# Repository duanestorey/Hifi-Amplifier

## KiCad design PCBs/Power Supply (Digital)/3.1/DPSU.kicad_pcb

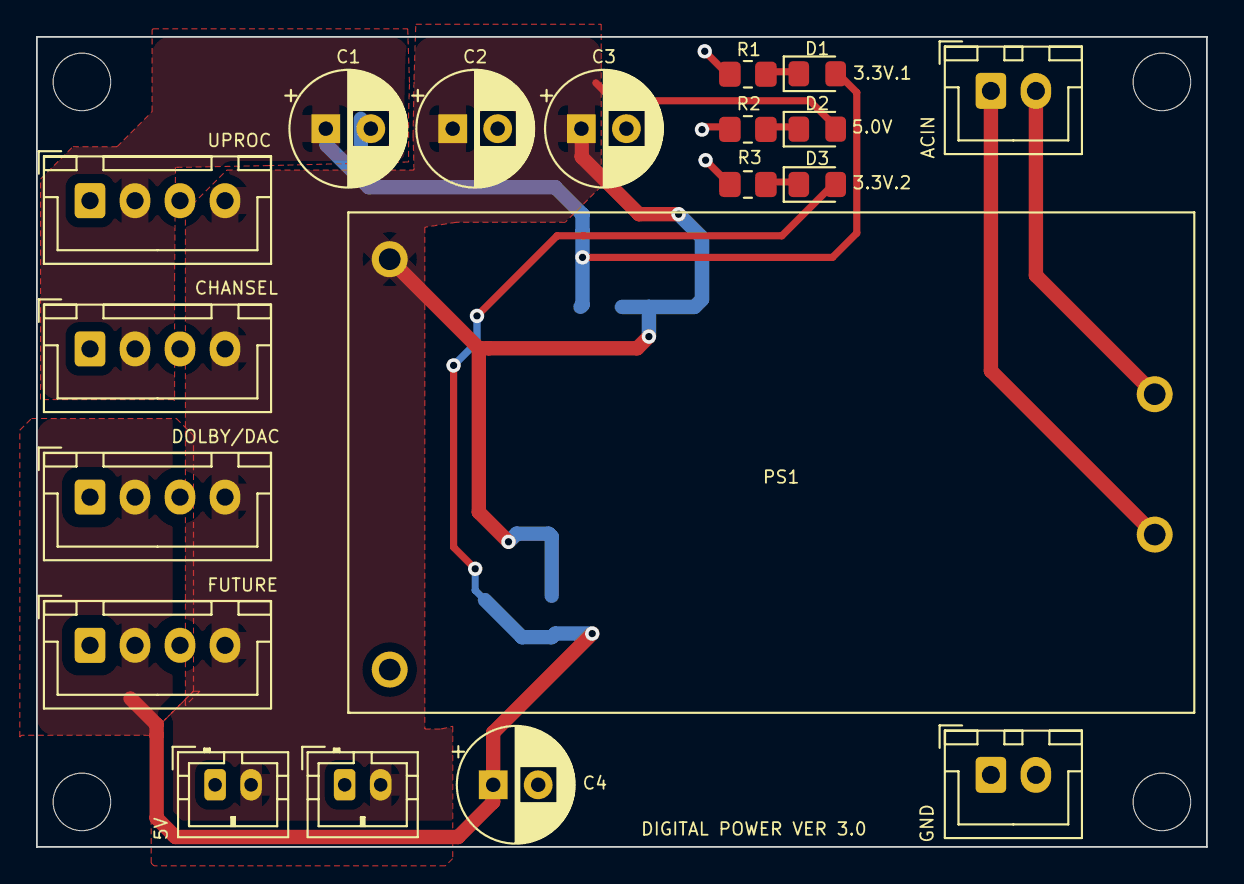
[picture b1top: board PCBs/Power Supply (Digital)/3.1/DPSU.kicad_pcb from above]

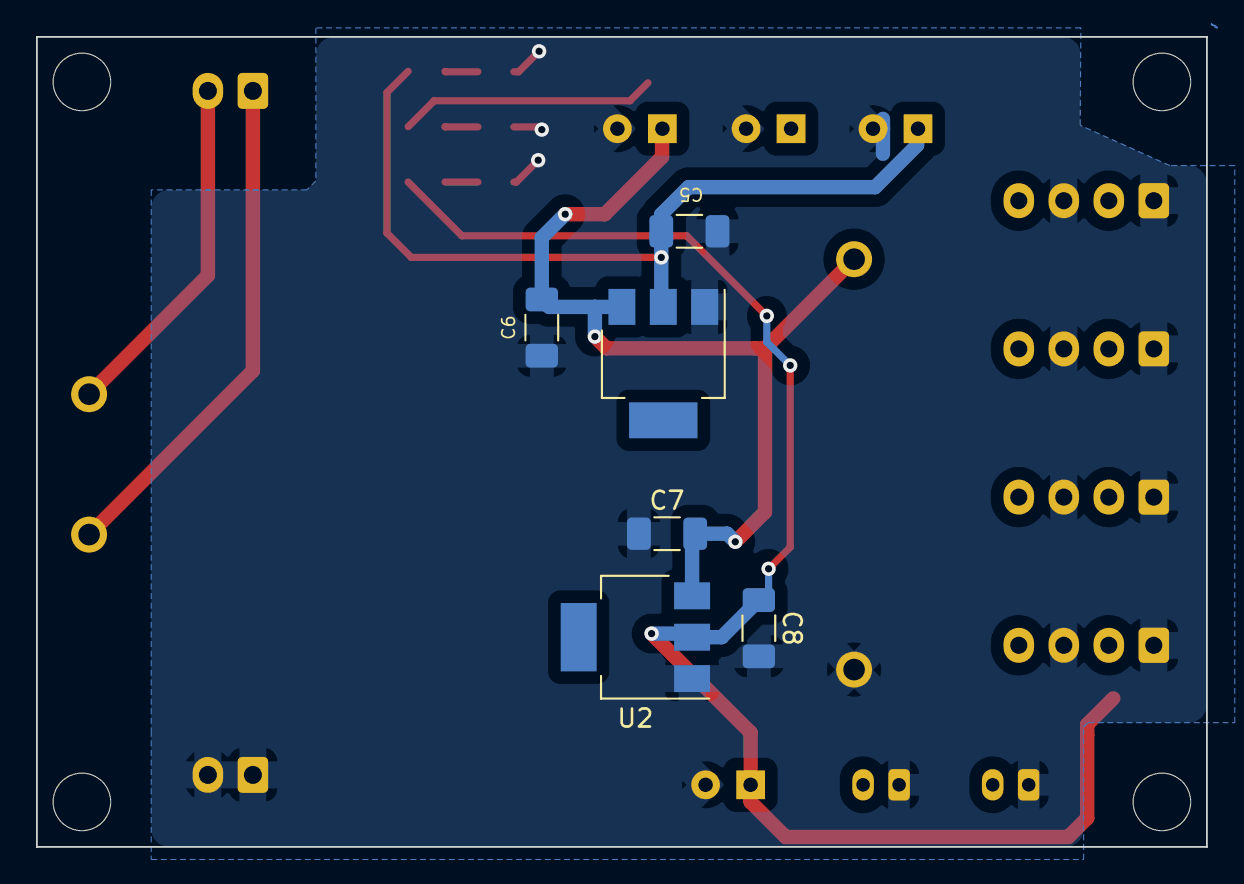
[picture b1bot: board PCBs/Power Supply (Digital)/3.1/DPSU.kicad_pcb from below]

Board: 2 copper layers, 65.0 x 45.0 mm, 29 parts (6 on the bottom side), 9 nets.

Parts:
C1, C2, C3, C4: 470u 10V; CP_Radial_D6.3mm_P2.50mm
C5, C8: 10U; C_1206_3216Metric_Pad1.33x1.80mm_HandSolder
C6, C7: 10u; C_1206_3216Metric_Pad1.33x1.80mm_HandSolder
D1, D3: WHITE; LED_0805_2012Metric_Pad1.15x1.40mm_HandSolder
D2: BLUE; LED_0805_2012Metric_Pad1.15x1.40mm_HandSolder
DIG1, DIG2: Conn_01x02_Male; JST_PH_B2B-PH-K_1x02_P2.00mm_Vertical
H1, H2, H3, H4: MountingHole; MountingHole_3.2mm_M3
J1: FUTURE; JST_XH_B4B-XH-A_1x04_P2.50mm_Vertical
J2: CHANSEL; JST_XH_B4B-XH-A_1x04_P2.50mm_Vertical
J3: DOLBY; JST_XH_B4B-XH-A_1x04_P2.50mm_Vertical
J4: UPRO; JST_XH_B4B-XH-A_1x04_P2.50mm_Vertical
J5, J6: Conn_01x02_Male; JST_XH_B2B-XH-A_1x02_P2.50mm_Vertical
PS1: HLK-10M05
R1, R3: 510R; R_0805_2012Metric_Pad1.20x1.40mm_HandSolder
R2: 750R; R_0805_2012Metric_Pad1.20x1.40mm_HandSolder
U1, U2: AZ1117CH2-3.3; SOT-223

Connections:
3V3: C1.1, C5.1, D1.2 (A), J1.2, J2.2, U1.2 (VO)
3V32: C4.1, C8.1, D3.2 (A), J3.2, J4.2, U2.2 (VO)
5V: C2.1, C3.1, C6.2, C7.2, D2.2 (A), DIG1.2, DIG2.2, J1.4, J2.4, J3.4, J4.4, PS1.4 (+Vout), U1.3 (VI), U2.3 (VI)
unnamed: D1.1 (K), R1.1
unnamed: D2.1 (K), R2.1
unnamed: D3.1 (K), R3.1
PGND: C1.2, C2.2, C3.2, C4.2, C5.2, C6.1, C7.1, C8.2, DIG1.1, DIG2.1, J1.1, J1.3, J2.1, J2.3, J3.1, J3.3, J4.1, J4.3, J5.1, J5.2, PS1.3 (-Vout), R1.2, R2.2, R3.2, U1.1 (GND), U2.1 (GND)
VIN: J6.1, PS1.1 (AC/L)
VNEG: J6.2, PS1.2 (AC/N)

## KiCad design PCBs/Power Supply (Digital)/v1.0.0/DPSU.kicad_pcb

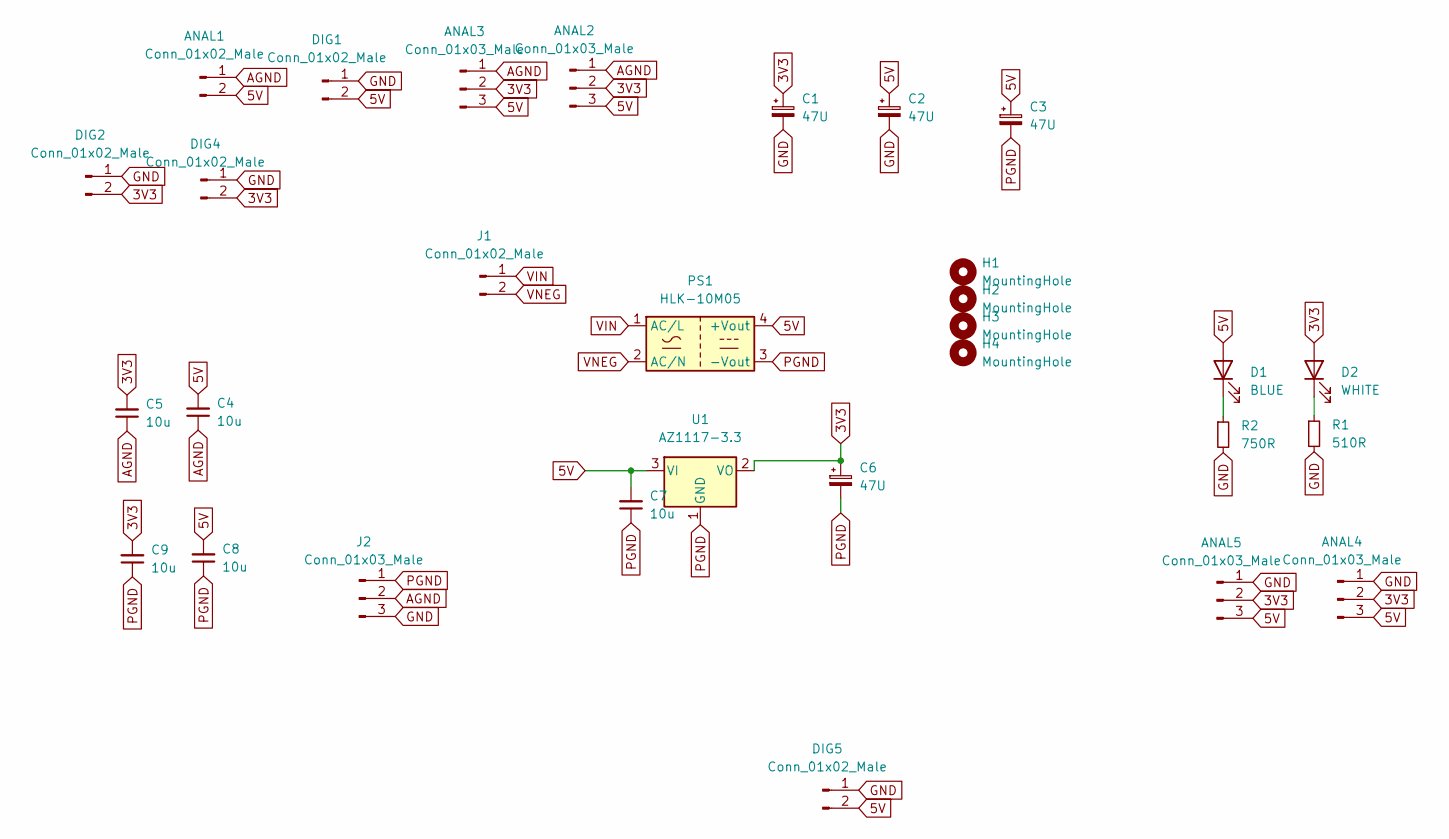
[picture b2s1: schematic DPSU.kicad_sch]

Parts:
ANAL1: Conn_01x02_Male; JST_PH_B2B-PH-K_1x02_P2.00mm_Vertical
ANAL2, ANAL3, ANAL4, ANAL5: Conn_01x03_Male; JST_PH_B3B-PH-K_1x03_P2.00mm_Vertical
C1, C2: 47U; CP_Radial_D6.3mm_P2.50mm
C3, C6: 47U; CP_Radial_D8.0mm_P5.00mm
C4, C5, C7, C8, C9: 10u; C_1206_3216Metric_Pad1.33x1.80mm_HandSolder
D1: BLUE; LED_0805_2012Metric_Pad1.15x1.40mm_HandSolder
D2: WHITE; LED_0805_2012Metric_Pad1.15x1.40mm_HandSolder
DIG1, DIG2, DIG4, DIG5: Conn_01x02_Male; JST_PH_B2B-PH-K_1x02_P2.00mm_Vertical
H1, H2, H3, H4: MountingHole; MountingHole_3.2mm_M3
J1: Conn_01x02_Male; JST_XH_B2B-XH-A_1x02_P2.50mm_Vertical
J2: Conn_01x03_Male; JST_PH_B3B-PH-K_1x03_P2.00mm_Vertical
PS1: HLK-10M05
R1: 510R; R_0805_2012Metric_Pad1.20x1.40mm_HandSolder
R2: 750R; R_0805_2012Metric_Pad1.20x1.40mm_HandSolder
U1: AZ1117-3.3; SOT-223

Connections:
3V3: ANAL2.2, ANAL3.2, ANAL4.2, ANAL5.2, C1.1, C5.2, C6.1, C9.2, D2.2 (A), DIG2.2, DIG4.2, U1.2 (VO)
5V: ANAL1.2, ANAL2.3, ANAL3.3, ANAL4.3, ANAL5.3, C2.1, C3.1, C4.2, C7.2, C8.2, D1.2 (A), DIG1.2, DIG5.2, PS1.4 (+Vout), U1.3 (VI)
AGND: ANAL1.1, ANAL2.1, ANAL3.1, C4.1, C5.1, J2.2
GND: ANAL4.1, ANAL5.1, C1.2, C2.2, DIG1.1, DIG2.1, DIG4.1, DIG5.1, J2.3, R1.2, R2.2
unnamed: D1.1 (K), R2.1
unnamed: D2.1 (K), R1.1
PGND: C3.2, C6.2, C7.1, C8.1, C9.1, J2.1, PS1.3 (-Vout), U1.1 (GND)
VIN: J1.1, PS1.1 (AC/L)
VNEG: J1.2, PS1.2 (AC/N)

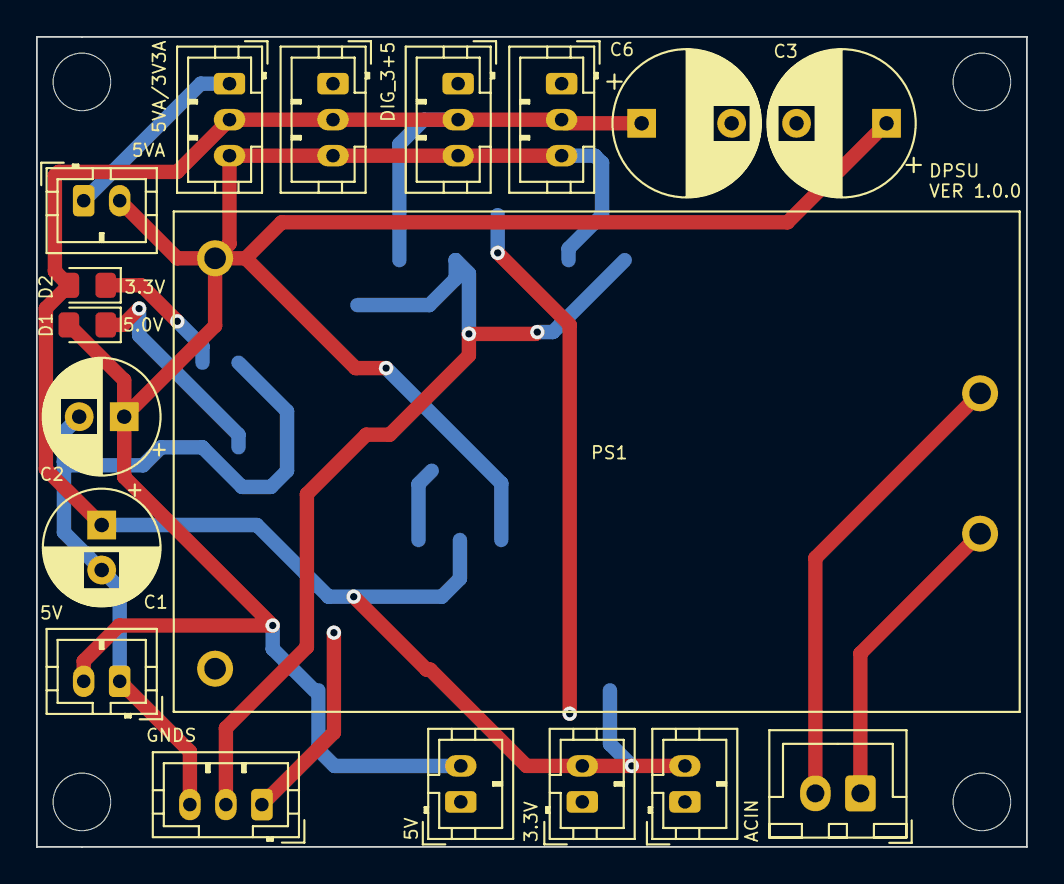
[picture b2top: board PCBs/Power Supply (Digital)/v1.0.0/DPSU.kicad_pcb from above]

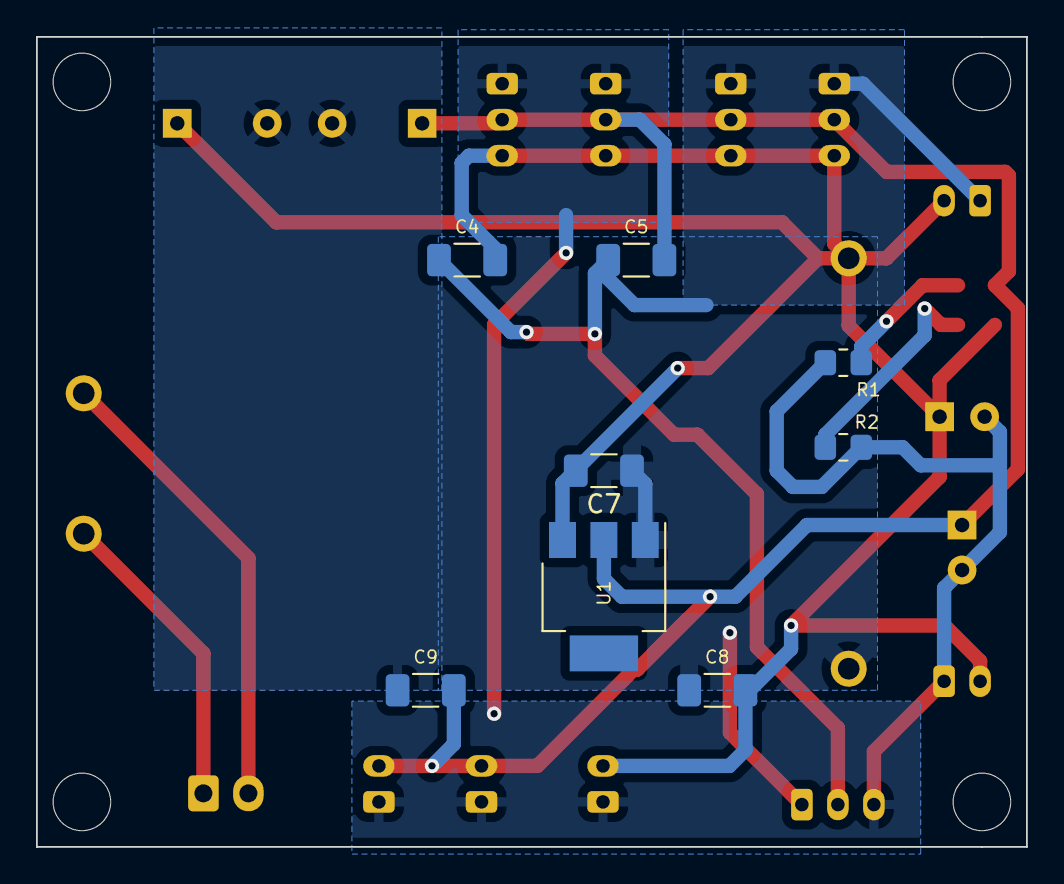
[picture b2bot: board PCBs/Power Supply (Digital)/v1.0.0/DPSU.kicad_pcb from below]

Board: 2 copper layers, 55.0 x 45.0 mm, 30 parts (8 on the bottom side), 9 nets.

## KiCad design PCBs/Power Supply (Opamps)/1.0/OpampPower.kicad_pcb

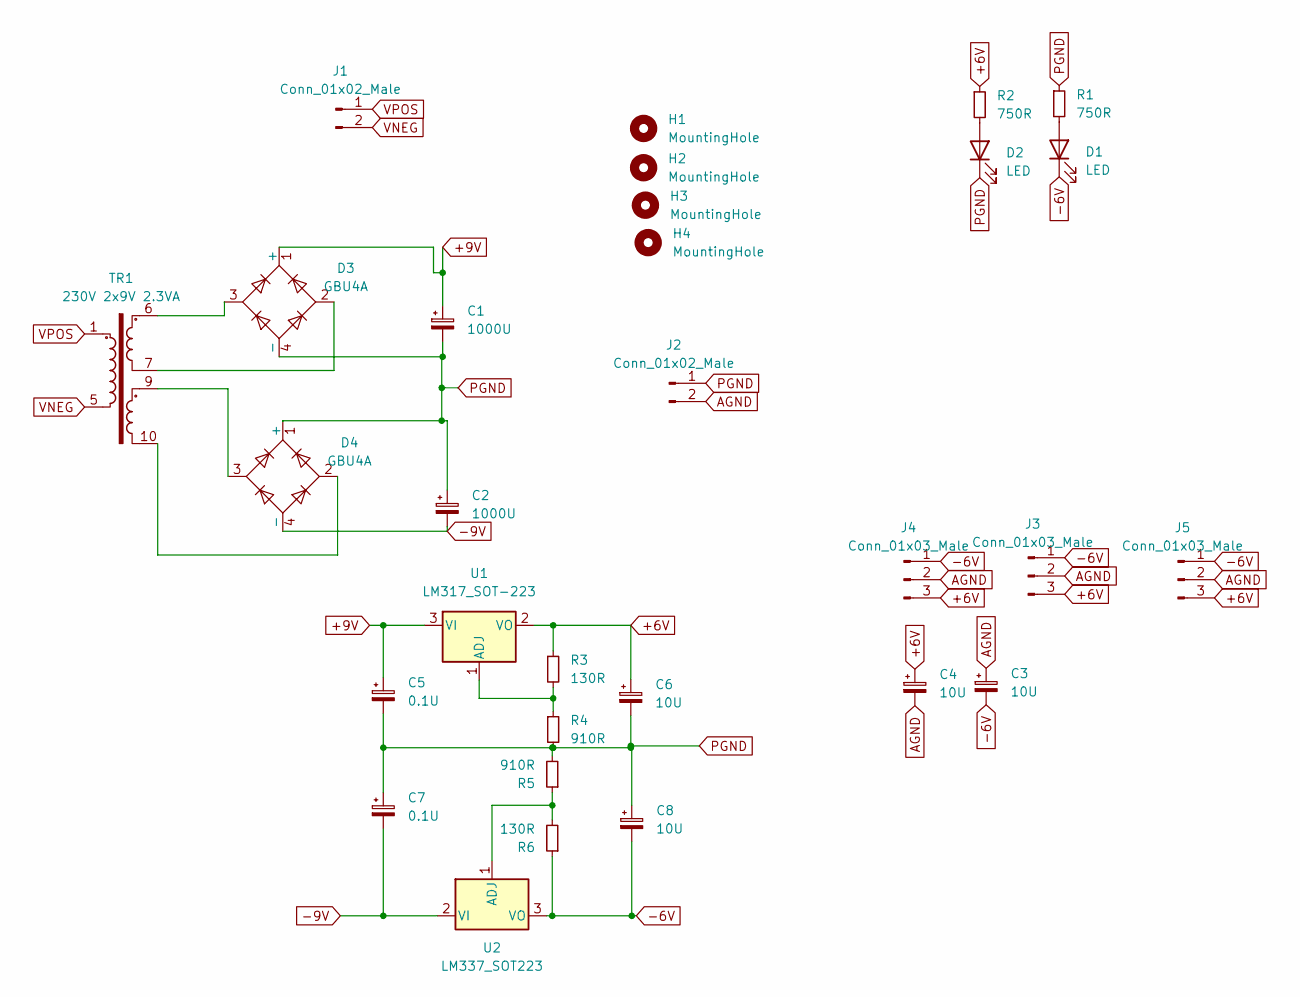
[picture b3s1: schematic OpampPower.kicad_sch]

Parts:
C1, C2: 1000U; CP_Radial_D10.0mm_P5.00mm_P7.50mm
C3, C4, C6, C8: 10U; C_1206_3216Metric_Pad1.33x1.80mm_HandSolder
C5, C7: 0.1U; C_0603_1608Metric_Pad1.08x0.95mm_HandSolder
D1, D2: LED; LED_0805_2012Metric_Pad1.15x1.40mm_HandSolder
D3, D4: GBU4A; Diode_Bridge_Vishay_GBU
H1, H2, H3, H4: MountingHole; MountingHole_3.2mm_M3
J1: Conn_01x02_Male; JST_XH_B2B-XH-A_1x02_P2.50mm_Vertical
J2: Conn_01x02_Male; JST_PH_B2B-PH-K_1x02_P2.00mm_Vertical
J3, J4, J5: Conn_01x03_Male; JST_PH_B3B-PH-K_1x03_P2.00mm_Vertical
R1, R2: 750R; R_0603_1608Metric_Pad0.98x0.95mm_HandSolder
R3, R6: 130R; R_0805_2012Metric_Pad1.20x1.40mm_HandSolder
R4, R5: 910R; R_0805_2012Metric_Pad1.20x1.40mm_HandSolder
TR1: 230V 2x9V 2.3VA; Transformer_Breve_TEZ-28x33
U1: LM317_SOT-223; SOT-223-3_TabPin2
U2: LM337_SOT223; SOT-223-3_TabPin2

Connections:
+6V: C4.1, C6.1, J3.3, J4.3, J5.3, R2.1, R3.1, U1.2 (VO)
+9V: C1.1, C5.1, D3.1 (+), U1.3 (VI)
-6V: C3.2, C8.2, D1.1 (K), J3.1, J4.1, J5.1, R6.1, U2.3 (VO)
-9V: C2.2, C7.2, D4.4 (-), U2.2 (VI)
AGND: C3.1, C4.2, J2.2, J3.2, J4.2, J5.2
unnamed: D1.2 (A), R1.2
unnamed: D2.2 (A), R2.2
unnamed: D3.2, TR1.7
unnamed: D3.3, TR1.6
unnamed: D4.2, TR1.10
unnamed: D4.3, TR1.9
unnamed: R3.2, R4.1, U1.1 (ADJ)
unnamed: R5.1, R6.2, U2.1 (ADJ)
PGND: C1.2, C2.1, C5.2, C6.2, C7.1, C8.1, D2.1 (K), D3.4 (-), D4.1 (+), J2.1, R1.1, R4.2, R5.2
VNEG: J1.2, TR1.5
VPOS: J1.1, TR1.1

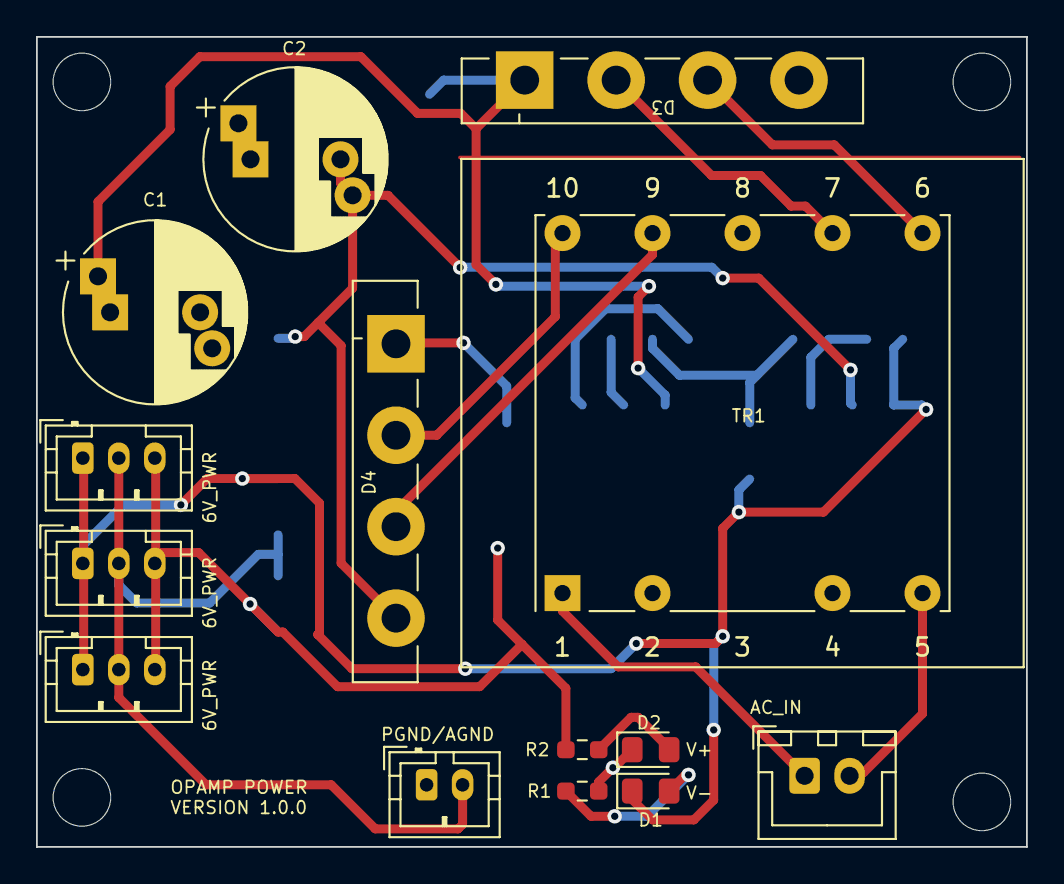
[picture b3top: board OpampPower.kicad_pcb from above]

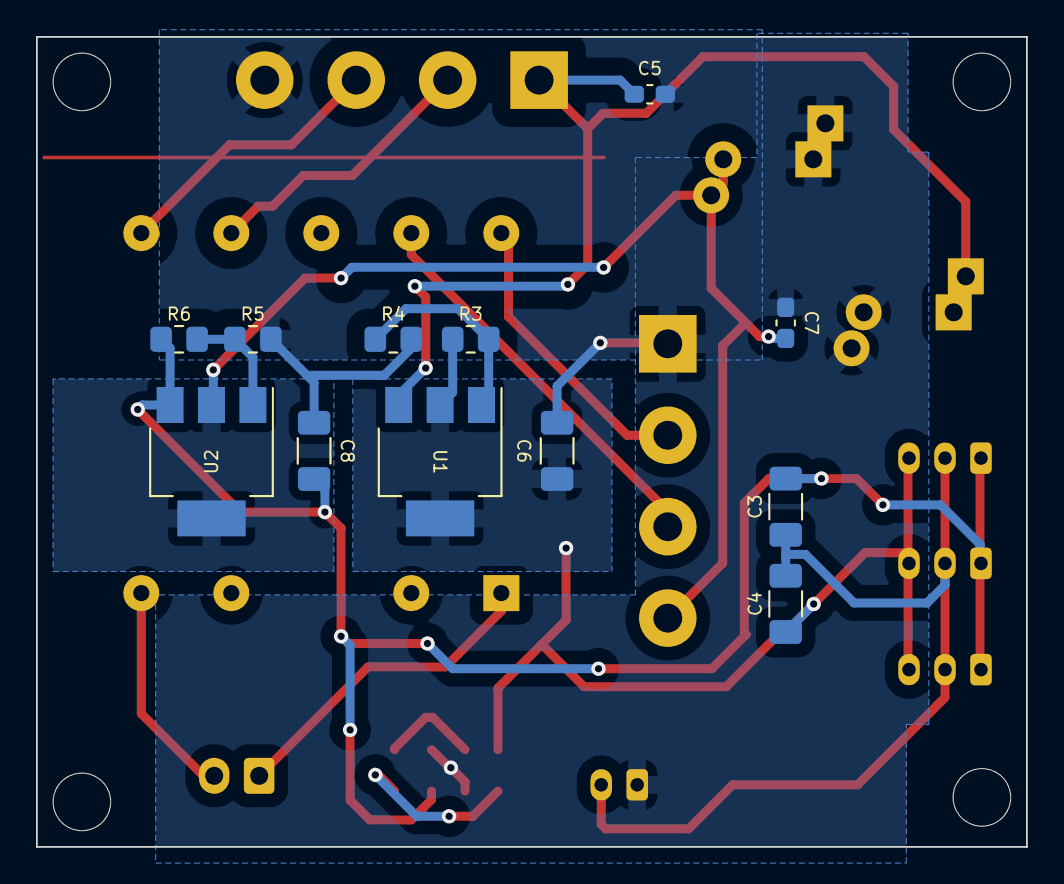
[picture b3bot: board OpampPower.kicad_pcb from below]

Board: 2 copper layers, 55.0 x 45.0 mm, 30 parts (12 on the bottom side), 16 nets.

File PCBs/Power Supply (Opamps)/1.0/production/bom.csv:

Designator,Footprint,Quantity,Value,LCSC Part #
"C1, C2",CP_Radial_D10.0mm_P5.00mm_P7.50mm,2,1000U,
"C3, C4, C6, C8",C_1206_3216Metric_Pad1.33x1.80mm_HandSolder,4,10U,
"C5, C7",C_0603_1608Metric_Pad1.08x0.95mm_HandSolder,2,0.1U,
"D1, D2",LED_0805_2012Metric_Pad1.15x1.40mm_HandSolder,2,LED,
"D3, D4",Diode_Bridge_Vishay_GBU,2,GBU4A,
"H1, H2, H3, H4",MountingHole_3.2mm_M3,4,MountingHole,
J1,JST_XH_B2B-XH-A_1x02_P2.50mm_Vertical,1,Conn_01x02_Male,
J2,JST_PH_B2B-PH-K_1x02_P2.00mm_Vertical,1,Conn_01x02_Male,
"J3, J4, J5",JST_PH_B3B-PH-K_1x03_P2.00mm_Vertical,3,Conn_01x03_Male,
"R1, R2",R_0603_1608Metric_Pad0.98x0.95mm_HandSolder,2,750R,
"R3, R6",R_0805_2012Metric_Pad1.20x1.40mm_HandSolder,2,220R,
"R4, R5",R_0805_2012Metric_Pad1.20x1.40mm_HandSolder,2,820R,
TR1,Transformer_Breve_TEZ-28x33,1,TEZ2.6-D-2,
U1,SOT-223-3_TabPin2,1,LM317_SOT-223,
U2,SOT-223-3_TabPin2,1,LM337_SOT223,

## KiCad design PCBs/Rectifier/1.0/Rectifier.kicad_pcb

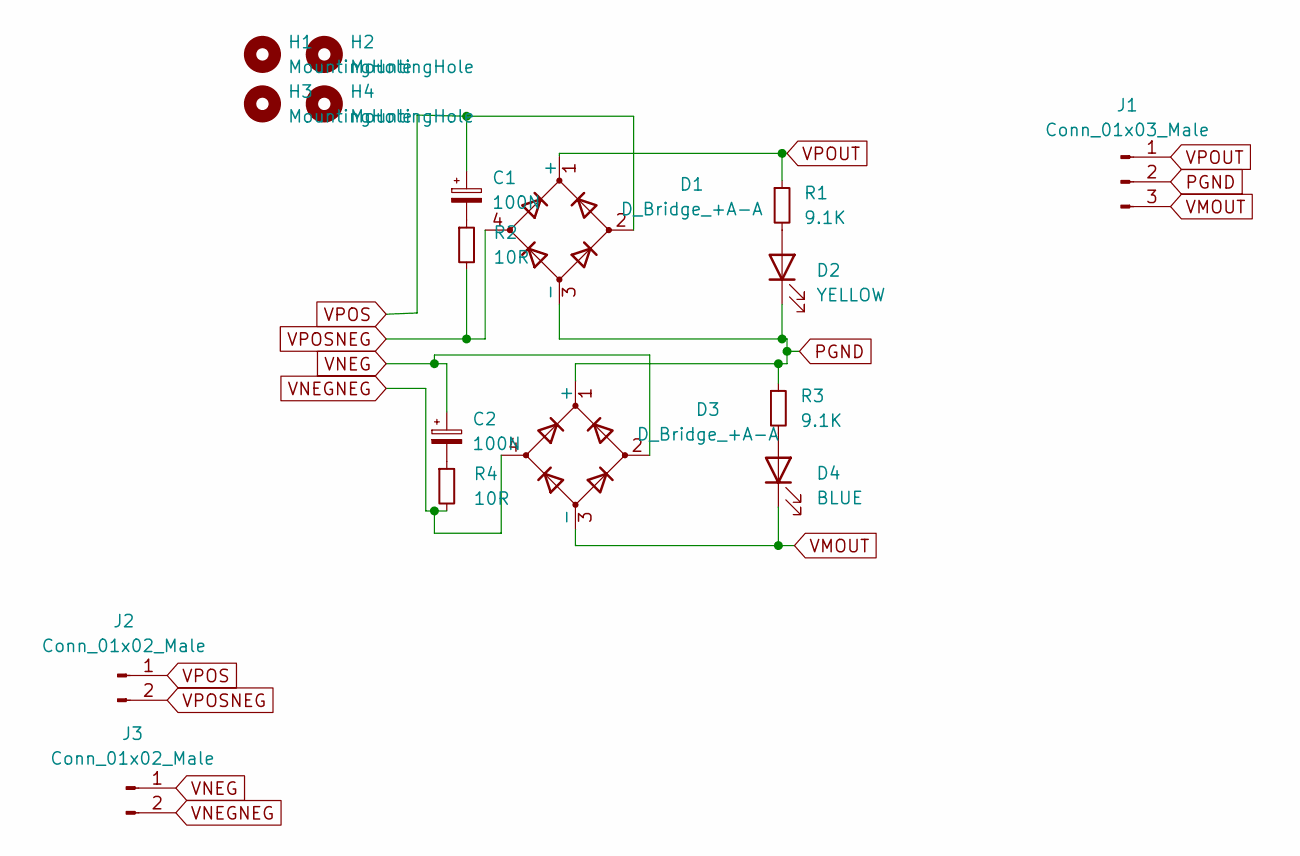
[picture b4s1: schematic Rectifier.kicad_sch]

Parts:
C1, C2: 100N; C_Rect_L13.0mm_W6.0mm_P10.00mm_FKS3_FKP3_MKS4
D1, D3: D_Bridge_+A-A; Diode_Bridge_19.0x19.0x6.8mm_P12.7mm
D2: YELLOW; LED_0805_2012Metric_Pad1.15x1.40mm_HandSolder
D4: BLUE; LED_0805_2012Metric_Pad1.15x1.40mm_HandSolder
H1, H3: MountingHole; MountingHole_3mm
H2, H4: MountingHole; MountingHole_3.2mm_M3
J1: Conn_01x03_Male; JST_VH_B3P-VH_1x03_P3.96mm_Vertical
J2, J3: Conn_01x02_Male; JST_VH_B2P-VH-B_1x02_P3.96mm_Vertical
R1, R3: 9.1K; R_0805_2012Metric_Pad1.20x1.40mm_HandSolder
R2, R4: 10R; R_Axial_DIN0411_L9.9mm_D3.6mm_P15.24mm_Horizontal

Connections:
unnamed: C1.2, R2.1
unnamed: C2.2, R4.1
unnamed: D2.2 (A), R1.2
unnamed: D4.2 (A), R3.2
PGND: D1.3 (-), D2.1 (K), D3.1 (+), J1.2, R3.1
VMOUT: D3.3 (-), D4.1 (K), J1.3
VNEG: C2.1, D3.2, J3.1
VNEGNEG: D3.4, J3.2, R4.2
VPOS: C1.1, D1.2, J2.1
VPOSNEG: D1.4, J2.2, R2.2
VPOUT: D1.1 (+), J1.1, R1.1

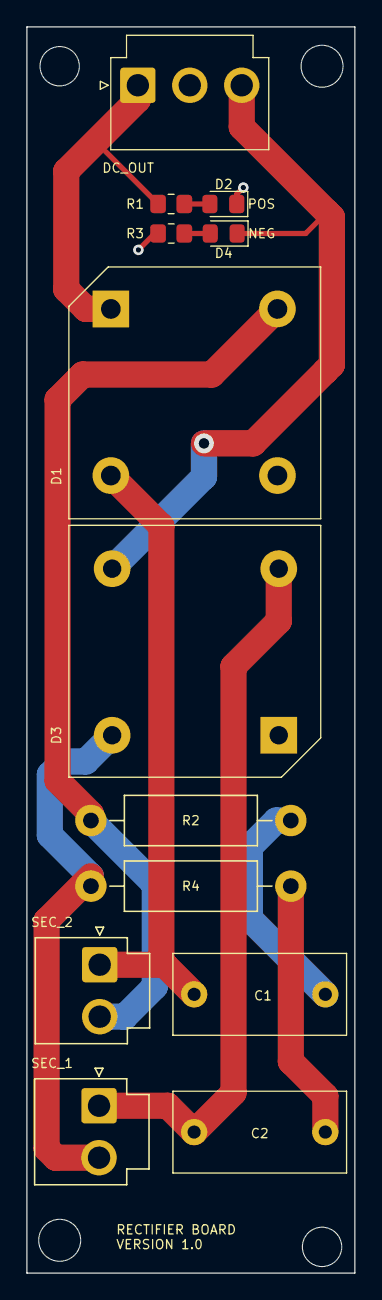
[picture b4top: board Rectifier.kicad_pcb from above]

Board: 2 copper layers, 25.0 x 95.0 mm, 17 parts (0 on the bottom side), 11 nets.

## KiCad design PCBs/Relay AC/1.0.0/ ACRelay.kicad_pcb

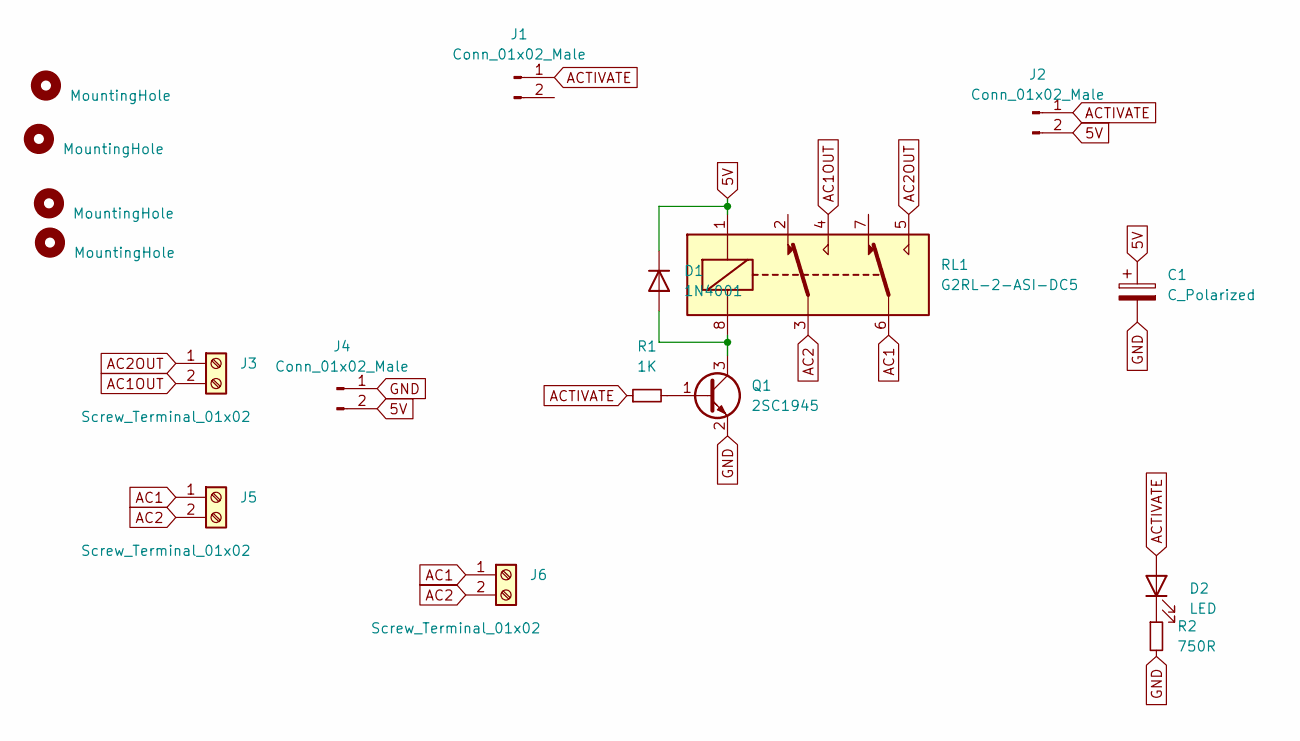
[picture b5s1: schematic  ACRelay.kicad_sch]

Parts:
C1: C_Polarized; CP_Radial_D8.0mm_P5.00mm
D1: 1N4001; D_SMA
D2: LED; D_0805_2012Metric_Pad1.15x1.40mm_HandSolder
H1, H2, H3, H4: MountingHole; MountingHole_3.2mm_M3
J1, J4: Conn_01x02_Male; JST_PH_B2B-PH-K_1x02_P2.00mm_Vertical
J2: Conn_01x02_Male; PinHeader_1x02_P2.54mm_Vertical
J3, J5, J6: Screw_Terminal_01x02; TerminalBlock_Phoenix_MKDS-1,5-2_1x02_P5.00mm_Horizontal
Q1: 2SC1945; SOT-23_Handsoldering
R1: 1K; R_0603_1608Metric
R2: 750R; R_0603_1608Metric_Pad0.98x0.95mm_HandSolder
RL1: G2RL-2-ASI-DC5; Relay_DPDT_Omron_G2RL

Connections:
5V: C1.1, D1.1 (K), J2.2, J4.2, RL1.1
AC1: J5.1, J6.1, RL1.6
AC1OUT: J3.2, RL1.4
AC2: J5.2, J6.2, RL1.3
AC2OUT: J3.1, RL1.5
ACTIVATE: D2.2 (A), J1.1, J2.1, R1.1
GND: C1.2, J4.1, Q1.2 (E), R2.2
unnamed: D1.2 (A), Q1.3 (C), RL1.8
unnamed: D2.1 (K), R2.1
unnamed: Q1.1 (B), R1.2

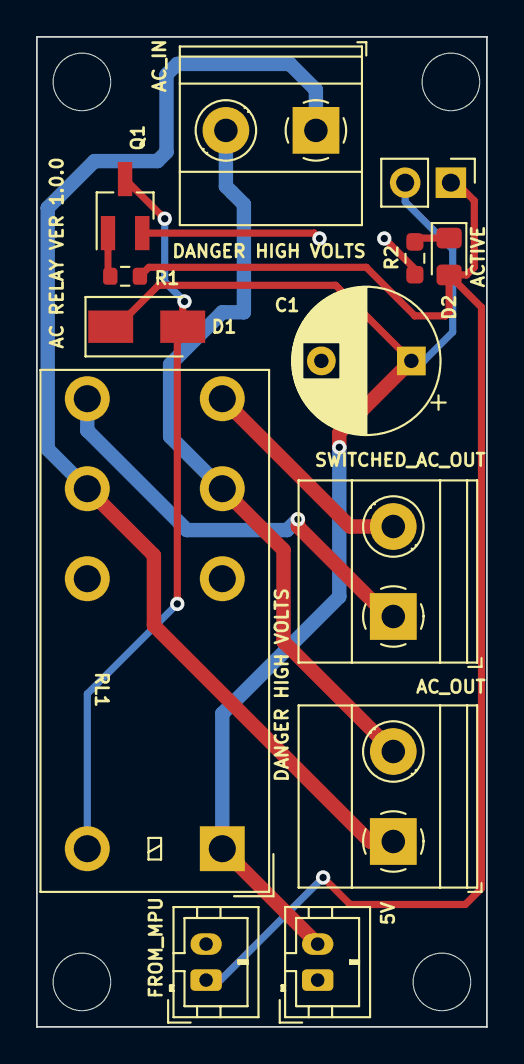
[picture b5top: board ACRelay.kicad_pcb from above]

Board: 2 copper layers, 25.0 x 55.0 mm, 17 parts (0 on the bottom side), 10 nets.
